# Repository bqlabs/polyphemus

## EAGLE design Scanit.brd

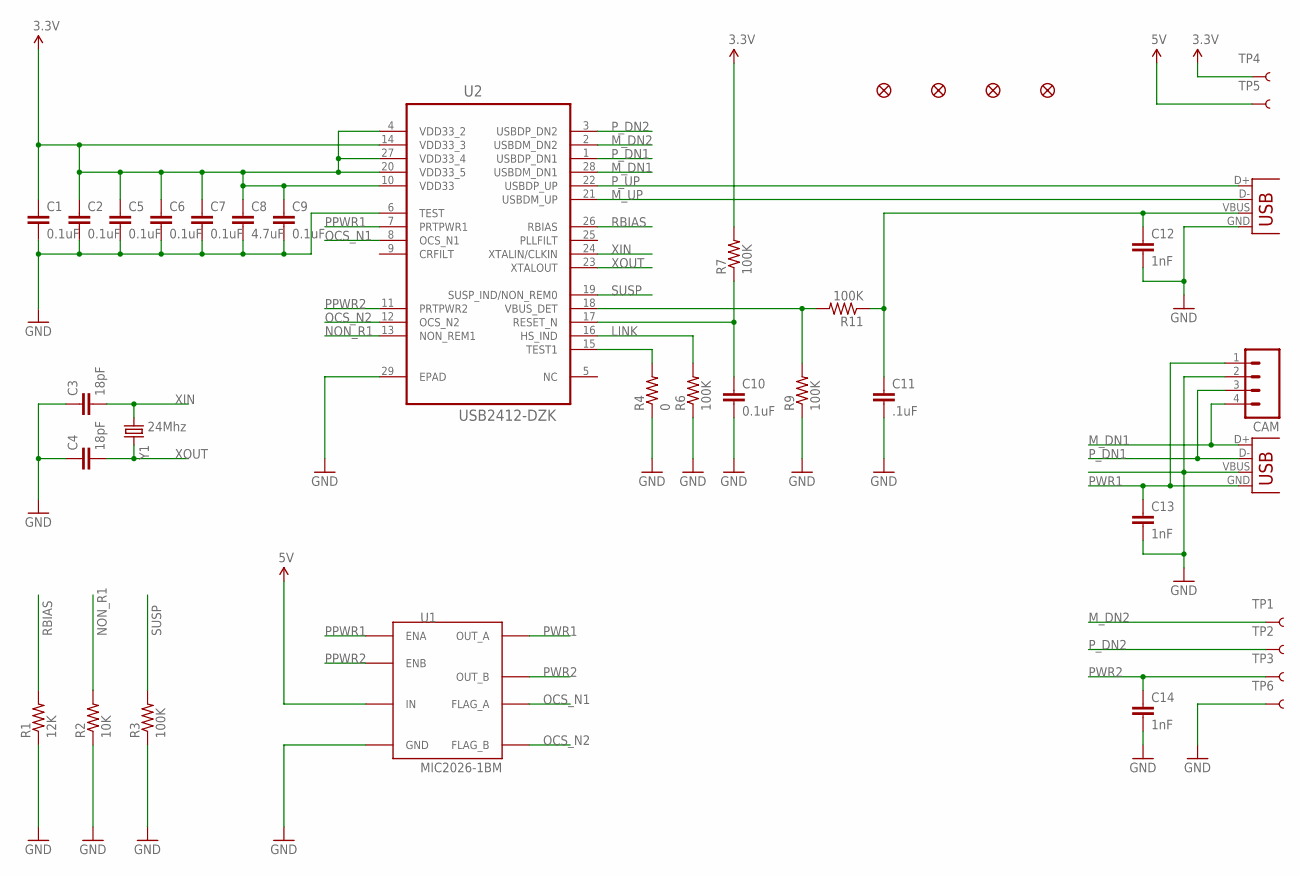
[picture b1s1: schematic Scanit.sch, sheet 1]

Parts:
C1, C2, C5, C6, C7, C9, C10: 0.1uF; 0603-CAP
C3, C4: 18pF; 0603-CAP
C8: 4.7uF; 0603-CAP
C11: .1uF; 0603-CAP
C12, C13, C14: 1nF; 0603-CAP
CAM: M04JST-PTH-VERT; JST-4-PTH-VERT
FID1, FID2, FID3, FID4: FIDUCIAL1X2; FIDUCIAL-1X2
R1: 12K; 0603-RES
R2: 10K; 0603-RES
R3, R6, R7, R9, R11: 100K; 0603-RES
R4: 0; 0603-RES
TP1, TP2, TP3, TP4, TP5, TP6: TEST-POINT3X5; PAD.03X.05
U1: MIC2026-1BM; SOP-8
U2: USB2412-DZK; QFN50P500X500X100-29N
USB: USBPTH-VERTICAL; USB-B-PTH-VERTICAL
USBCAM: USB-A-S
Y1: 24Mhz; CRYSTAL-SMD-5X3

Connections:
3.3V: C1.1, C2.1, C5.1, C6.1, C7.1, C8.1, C9.1, R7.2, TP4.P$1, U2.4 (VDD33_2), U2.10 (VDD33), U2.14 (VDD33_3), U2.20 (VDD33_5), U2.27 (VDD33_4); also elsewhere on the board
5V: TP5.P$1, U1.7 (IN); also elsewhere on the board
GND: C1.2, C2.2, C3.1, C4.1, C5.2, C6.2, C7.2, C8.2, C9.2, C10.2, C11.2, C12.2, C13.2, C14.2, CAM.2, R1.1, R2.1, R3.1, R4.1, R6.1, R9.1, TP6.P$1, U1.6 (GND), U2.6 (TEST), U2.29 (EPAD), USB.GND, USBCAM.VBUS; also elsewhere on the board
LINK: R6.2, U2.16 (HS_IND)
M_DN1: CAM.4, U2.28 (USBDM_DN1), USBCAM.D+
M_DN2: TP1.P$1, U2.2 (USBDM_DN2); also elsewhere on the board
M_UP: U2.21 (USBDM_UP), USB.D-
unnamed: R4.2, U2.15 (TEST1)
unnamed: C10.1, R7.1, U2.17 (RESET_N)
unnamed: R9.2, R11.2, U2.18 (VBUS_DET)
unnamed: C11.1, C12.1, R11.1, USB.VBUS
NON_R1: R2.2, U2.13 (NON_REM1)
OCS_N1: U1.2 (FLAG_A), U2.8 (OCS_N1)
OCS_N2: U1.3 (FLAG_B), U2.12 (OCS_N2)
PPWR1: U1.1 (ENA), U2.7 (PRTPWR1)
PPWR2: U1.4 (ENB), U2.11 (PRTPWR2)
PWR1: C13.1, CAM.1, U1.8 (OUT_A), USBCAM.GND
PWR2: C14.1, TP3.P$1, U1.5 (OUT_B); also elsewhere on the board
P_DN1: CAM.3, U2.1 (USBDP_DN1), USBCAM.D-
P_DN2: TP2.P$1, U2.3 (USBDP_DN2); also elsewhere on the board
P_UP: U2.22 (USBDP_UP), USB.D+
RBIAS: R1.2, U2.26 (RBIAS)
SUSP: R3.2, U2.19 (SUSP_IND/NON_REM0)
XIN: C3.2, U2.24 (XTALIN/CLKIN), Y1.1
XOUT: C4.2, U2.23 (XTALOUT), Y1.3 (2)

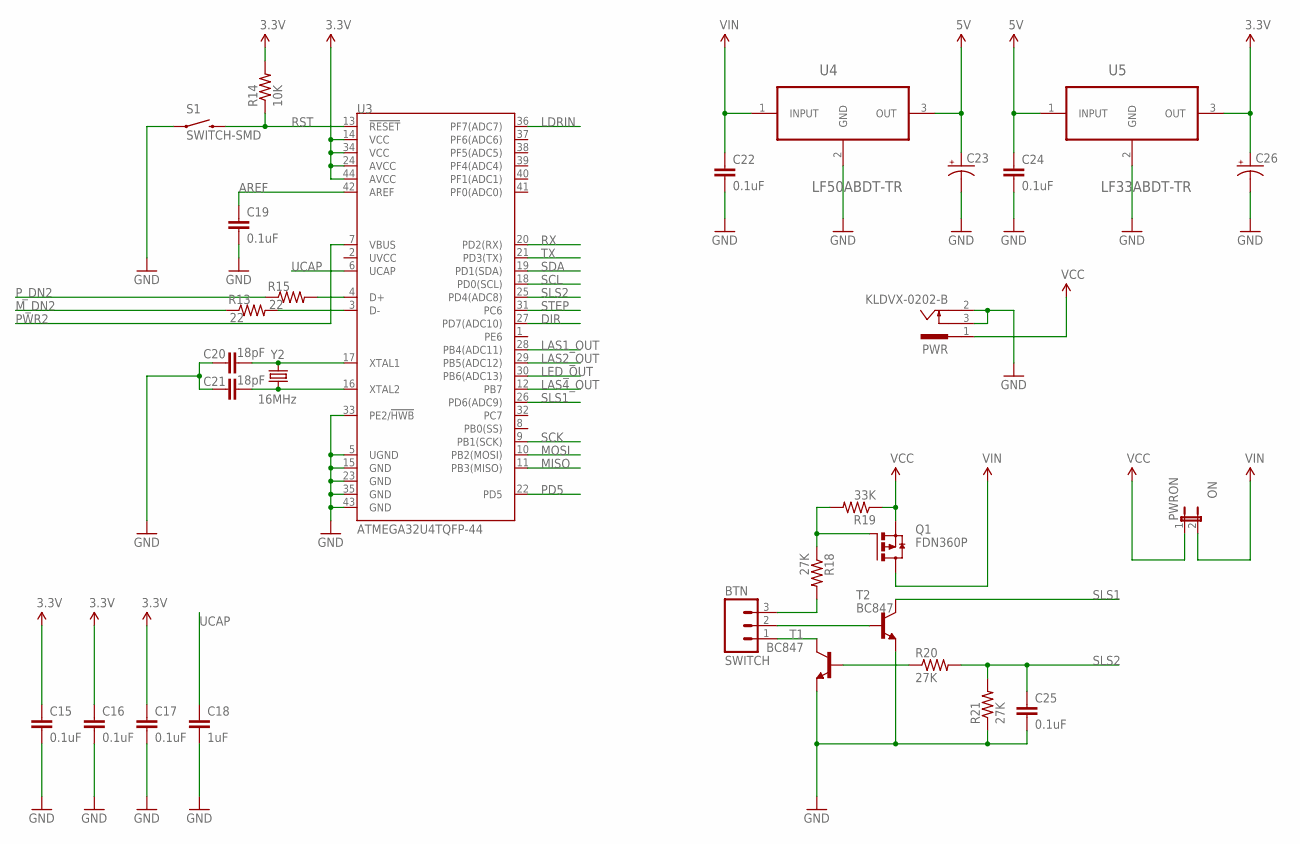
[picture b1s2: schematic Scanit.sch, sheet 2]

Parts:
BTN: SWITCH; JST-3-PTH-VERT
C15, C16, C17, C19, C25: 0.1uF; 0603-CAP
C18: 1uF; 0603-CAP
C20, C21: 18pF; 0603-CAP
C22, C24: 0.1uF; 1210
C23, C26: CAP_POLD; PANASONIC_D
PWR: KLDVX-0202-B
PWRON: ON; 1X02
Q1: FDN360P; SUPER-SOT3
R13, R15: 22; 0402-RES
R14: 10K; 0603-RES
R18, R20, R21: 27K; 0603-RES
R19: 33K; 0603-RES
S1: SWITCH-SMD; TACTILE_SWITCH_SMD
T1, T2: BC847; SOT23
U3: ATMEGA32U4TQFP-44; TQFP44
U4: LF50ABDT-TR; TO228P972X240-3N
U5: LF33ABDT-TR; TO228P972X240-3N
Y2: 16MHz; CRYSTAL-SMD-5X3

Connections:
3.3V: C15.1, C16.1, C17.1, C26.+, R14.2, U3.14 (VCC), U3.24 (AVCC), U3.34 (VCC), U3.44 (AVCC), U5.3 (OUT); also elsewhere on the board
5V: C23.+, C24.1, U4.3 (OUT), U5.1 (INPUT); also elsewhere on the board
AREF: C19.1, U3.42 (AREF)
DIR: U3.27 (PD7(ADC10)); also elsewhere on the board
GND: C15.2, C16.2, C17.2, C18.2, C19.2, C20.1, C21.1, C22.2, C23.-, C24.2, C25.2, C26.-, PWR.2, PWR.3, R21.1, S1.1, T1.2 (E), T2.2 (E), U3.5 (UGND), U3.15 (GND), U3.23 (GND), U3.33 (PE2/!HWB), U3.35 (GND), U3.43 (GND), U4.2 (GND), U5.2 (GND); also elsewhere on the board
LAS1_OUT: U3.28 (PB4(ADC11)); also elsewhere on the board
LAS2_OUT: U3.29 (PB5(ADC12)); also elsewhere on the board
LAS4_OUT: U3.12 (PB7)
LDRIN: U3.36 (PF7(ADC7)); also elsewhere on the board
LED_OUT: U3.30 (PB6(ADC13)); also elsewhere on the board
MISO: U3.11 (PB3(MISO)); also elsewhere on the board
MOSI: U3.10 (PB2(MOSI)); also elsewhere on the board
M_DN2: R13.1; also elsewhere on the board
unnamed: C20.2, U3.17 (XTAL1), Y2.3 (2)
unnamed: C21.2, U3.16 (XTAL2), Y2.1
unnamed: R15.2, U3.4 (D+)
unnamed: R13.2, U3.3 (D-)
unnamed: BTN.1, T1.3 (C)
unnamed: Q1.1 (G), R18.1, R19.2
unnamed: BTN.3, R18.2
unnamed: BTN.2, T2.1 (B)
unnamed: R20.1, T1.1 (B)
PD5: U3.22 (PD5)
PWR2: U3.7 (VBUS); also elsewhere on the board
P_DN2: R15.1; also elsewhere on the board
RST: R14.1, S1.3 (2), U3.13 (!RESET); also elsewhere on the board
RX: U3.20 (PD2(RX))
SCK: U3.9 (PB1(SCK)); also elsewhere on the board
SCL: U3.18 (PD0(SCL))
SDA: U3.19 (PD1(SDA))
SLS1: T2.3 (C), U3.26 (PD6(ADC9))
SLS2: C25.1, R20.2, R21.2, U3.25 (PD4(ADC8))
STEP: U3.31 (PC6); also elsewhere on the board
TX: U3.21 (PD3(TX))
UCAP: C18.1, U3.6 (UCAP)
VCC: PWR.1, PWRON.1, Q1.2 (S), R19.1
VIN: C22.1, PWRON.2, Q1.3 (D), U4.1 (INPUT); also elsewhere on the board

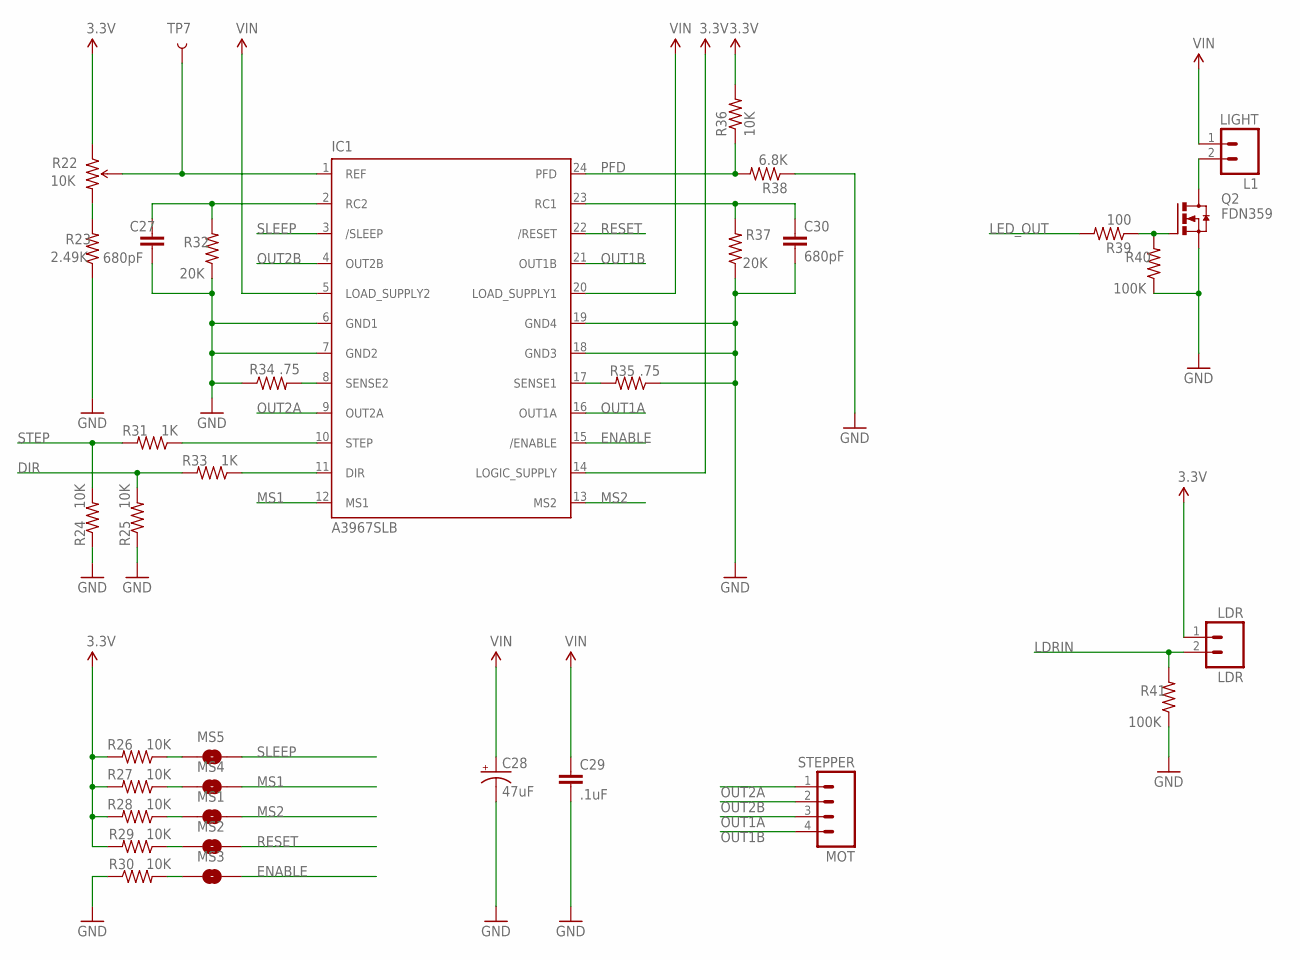
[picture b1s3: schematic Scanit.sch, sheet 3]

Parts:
C27, C30: 680pF; 0603-CAP
C28: 47uF; PANASONIC_D
C29: .1uF; 0603-CAP
IC1: A3967SLB; SO24W
L1: LIGHT; JST-2-PTH-VERT
LDR: LDR; JST-2-PTH-VERT
MOT: STEPPER; JST-4-PTH-VERT
MS1, MS2, MS3, MS4, MS5: SOLDERJUMPERTRACE; SJ_2S-TRACE
Q2: FDN359; SUPER-SOT3
R22: 10K; TRIMPOT-3MM-2
R23: 2.49K; 0603-RES
R24, R25, R26, R27, R28, R29, R30, R36: 10K; 0603-RES
R31, R33: 1K; 0603-RES
R32, R37: 20K; 0603-RES
R34, R35: .75; 0805
R38: 6.8K; 0603-RES
R39: 100; 0603-RES
R40, R41: 100K; 0603-RES
TP7: TEST-POINTTP_15TH_THRU; TP_15TH

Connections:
3.3V: IC1.14 (LOGIC_SUPPLY), LDR.1, R22.1 (CCW), R26.2, R27.2, R28.2, R29.2, R36.2; also elsewhere on the board
DIR: R25.2, R33.2; also elsewhere on the board
ENABLE: IC1.15 (/ENABLE), MS3.2
GND: C27.2, C28.-, C29.2, C30.2, IC1.6 (GND1), IC1.7 (GND2), IC1.18 (GND3), IC1.19 (GND4), Q2.2 (S), R23.1, R24.1, R25.1, R30.1, R32.1, R34.1, R35.1, R37.1, R38.1, R40.1, R41.1; also elsewhere on the board
LDRIN: LDR.2, R41.2; also elsewhere on the board
LED_OUT: R39.2; also elsewhere on the board
MS1: IC1.12 (MS1), MS4.2
MS2: IC1.13 (MS2), MS1.2
unnamed: IC1.8 (SENSE2), R34.2
unnamed: IC1.17 (SENSE1), R35.2
unnamed: C27.1, IC1.2 (RC2), R32.2
unnamed: C30.1, IC1.23 (RC1), R37.2
unnamed: R22.3 (CW), R23.2
unnamed: IC1.10 (STEP), R31.1
unnamed: IC1.11 (DIR), R33.1
unnamed: MS5.1, R26.1
unnamed: MS4.1, R27.1
unnamed: MS1.1, R28.1
unnamed: MS2.1, R29.1
unnamed: MS3.1, R30.2
unnamed: Q2.1 (G), R39.1, R40.2
unnamed: L1.2, Q2.3 (D)
OUT1A: IC1.16 (OUT1A), MOT.3
OUT1B: IC1.21 (OUT1B), MOT.4
OUT2A: IC1.9 (OUT2A), MOT.1
OUT2B: IC1.4 (OUT2B), MOT.2
PFD: IC1.24 (PFD), R36.1, R38.2
RESET: IC1.22 (/RESET), MS2.2
SLEEP: IC1.3 (/SLEEP), MS5.2
STEP: R24.2, R31.2; also elsewhere on the board
VIN: C28.+, C29.1, IC1.5 (LOAD_SUPPLY2), IC1.20 (LOAD_SUPPLY1); also elsewhere on the board
VREF: IC1.1 (REF), R22.2 (WIPER), TP7.P$1

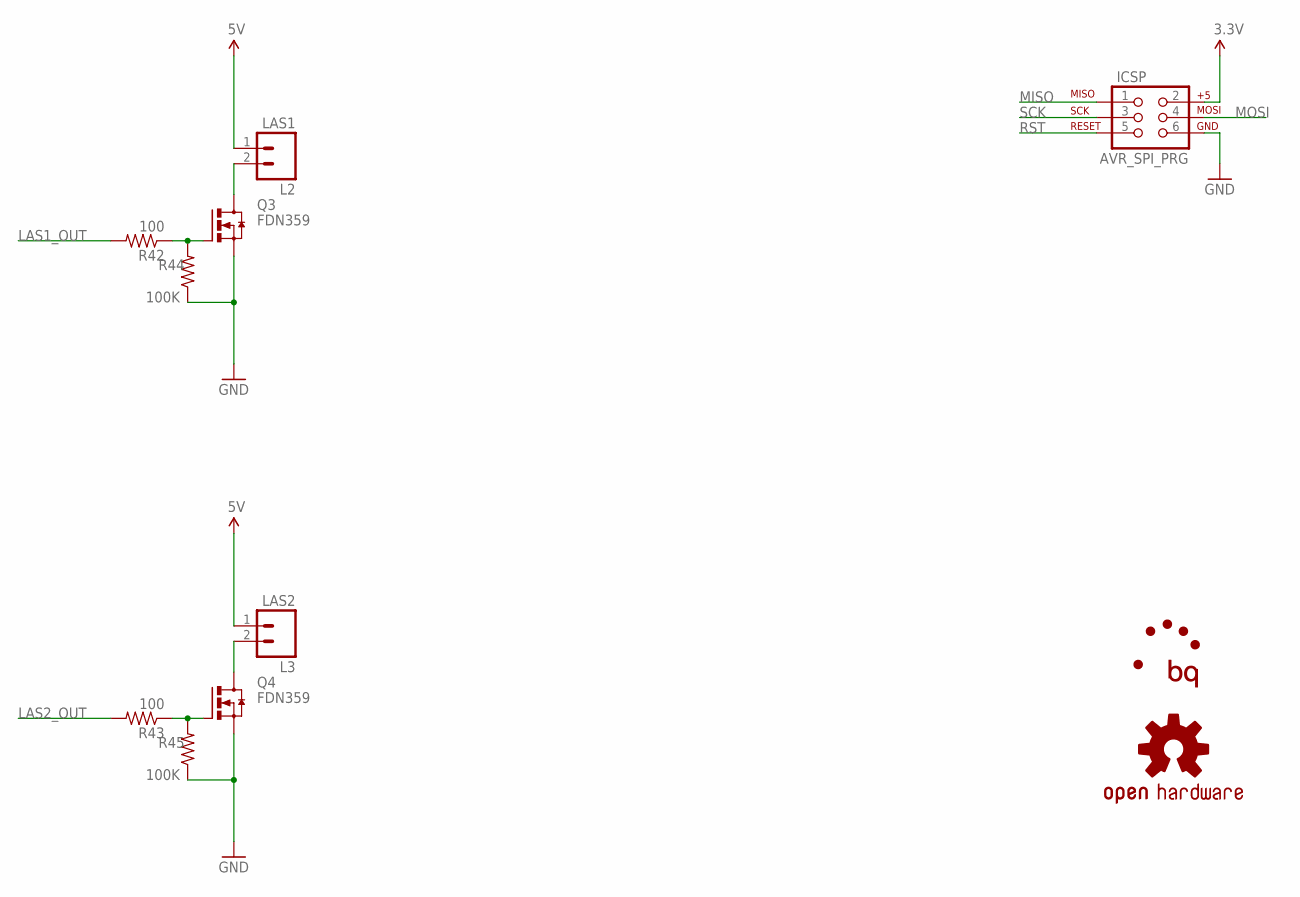
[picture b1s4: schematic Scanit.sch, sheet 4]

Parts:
ICSP: AVR_SPI_PRG; 2X3
L2: LAS1; JST-2-PTH-VERT
L3: LAS2; JST-2-PTH-VERT
LOGO2: OSHW-LOGOM; OSHW-LOGO-M
Q3, Q4: FDN359; SUPER-SOT3
R42, R43: 100; 0603-RES
R44, R45: 100K; 0603-RES

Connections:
3.3V: ICSP.2; also elsewhere on the board
5V: L2.1, L3.1; also elsewhere on the board
GND: ICSP.6, Q3.2 (S), Q4.2 (S), R44.1, R45.1; also elsewhere on the board
LAS1_OUT: R42.2; also elsewhere on the board
LAS2_OUT: R43.2; also elsewhere on the board
MISO: ICSP.1; also elsewhere on the board
MOSI: ICSP.4; also elsewhere on the board
unnamed: Q3.1 (G), R42.1, R44.2
unnamed: L2.2, Q3.3 (D)
unnamed: Q4.1 (G), R43.1, R45.2
unnamed: L3.2, Q4.3 (D)
RST: ICSP.5; also elsewhere on the board
SCK: ICSP.3; also elsewhere on the board

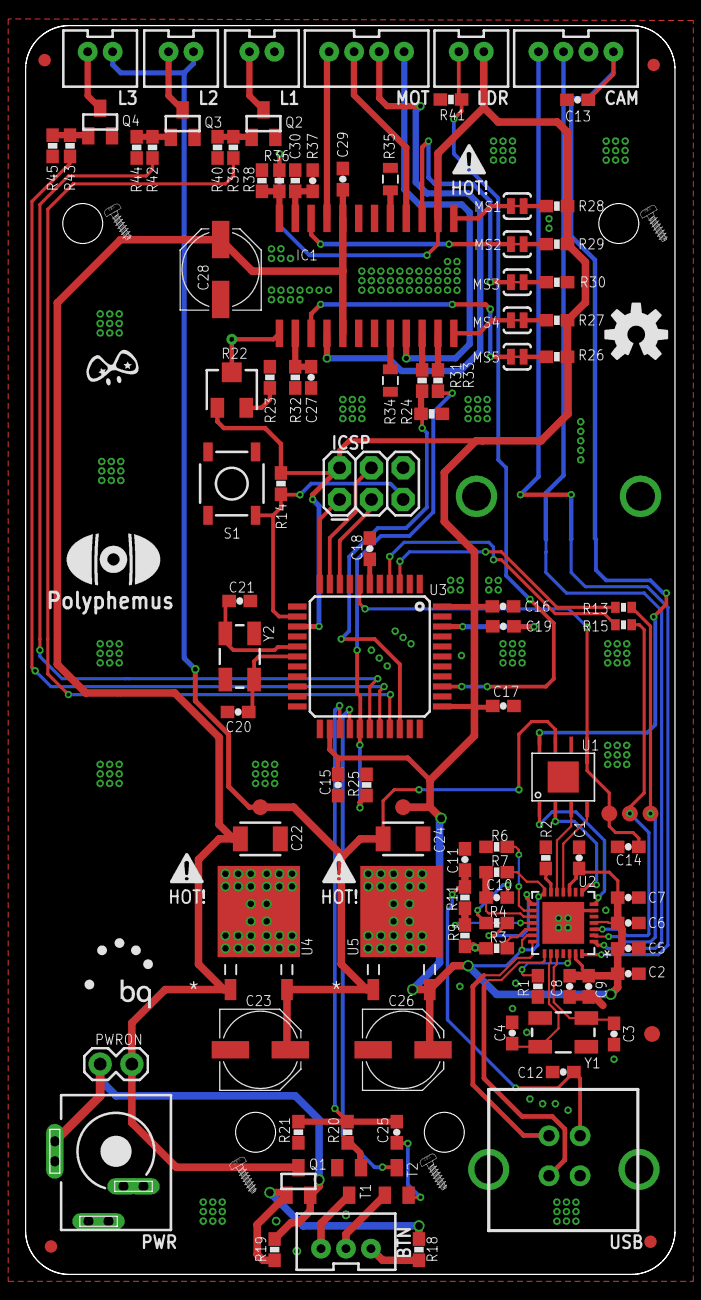
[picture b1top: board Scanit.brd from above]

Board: 2 copper layers, 52.0 x 100.0 mm, 123 parts (1 on the bottom side), 79 nets.

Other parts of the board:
U$1, U$2, U$3, U$12: SCREW
U$4, U$5, U$11: S_ATTENTION
U$6: SCANIT_LOGO
U$22: BQ_LOGO_SMALL
U$23: PIGHIXXX_LOGO

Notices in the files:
parts and their libraries:
SparkFun-Capacitors: Licensing: Creative Commons ShareAlike 4.0 International - https://creativecommons.org/licenses/by-sa/4.0
